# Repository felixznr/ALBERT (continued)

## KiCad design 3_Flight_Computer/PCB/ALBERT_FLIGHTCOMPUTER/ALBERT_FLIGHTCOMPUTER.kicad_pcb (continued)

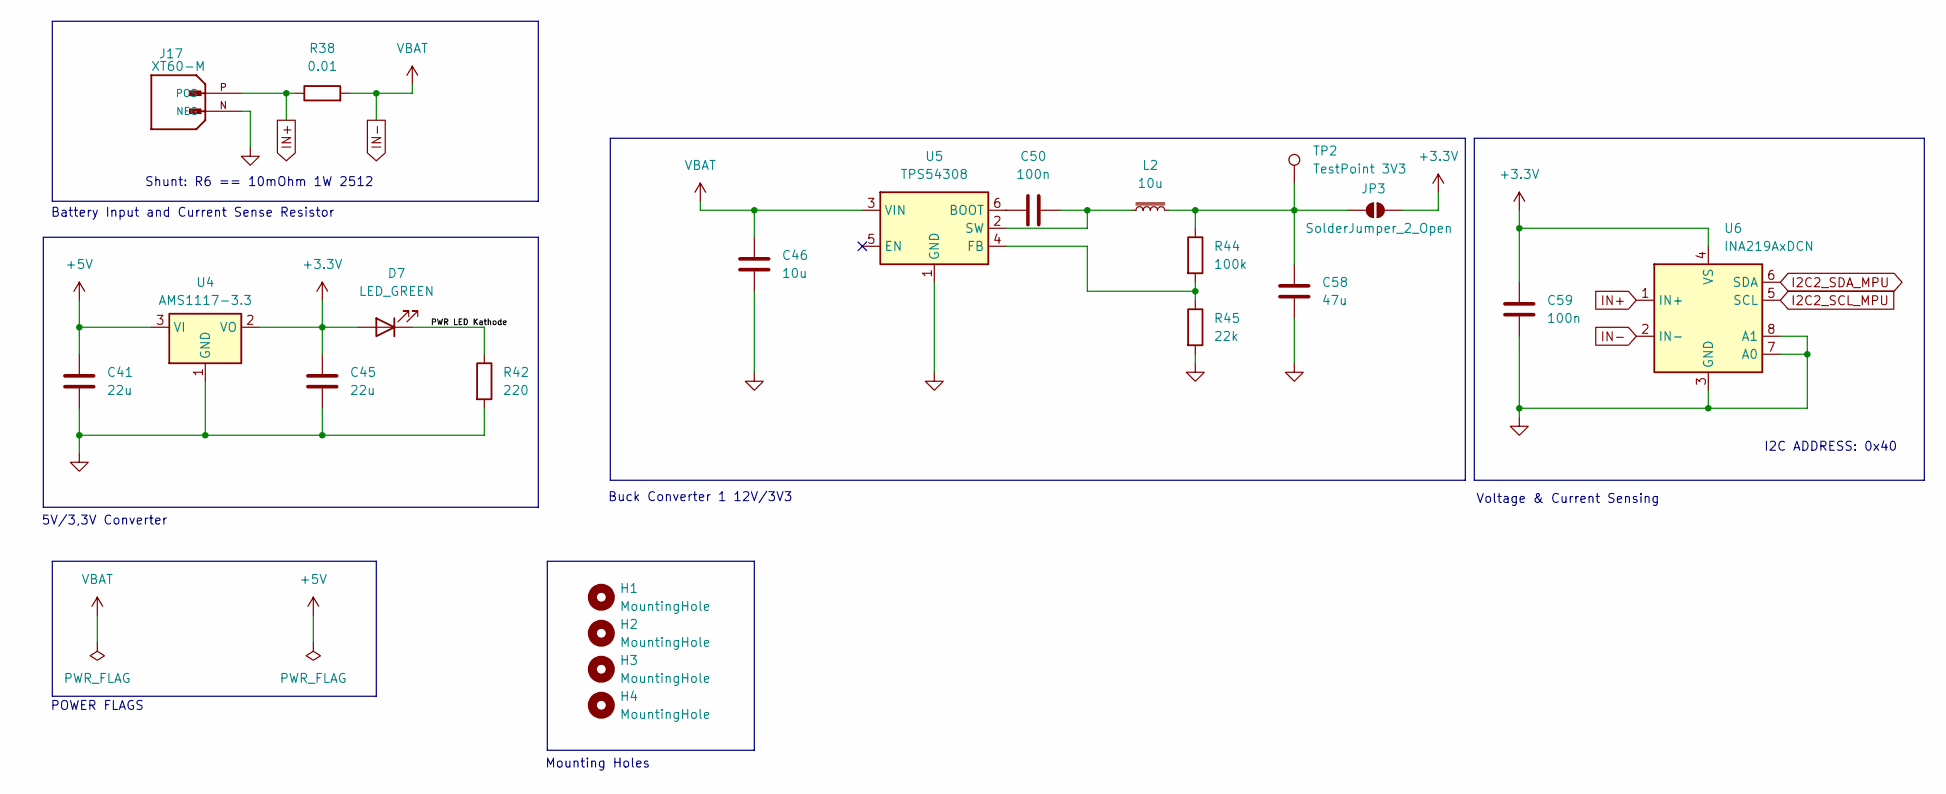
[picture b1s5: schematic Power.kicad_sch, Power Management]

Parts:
C41, C45: 22u; C_0805_2012Metric; LCSC C45783
C46: 10u; CAPC3225X270N; LCSC C380537
C50, C59: 100n; C_0402_1005Metric; LCSC C1525
C58: 47u; CAPC3225X270N; LCSC C77101
D7: LED_GREEN; LED_0603_1608Metric
H1, H2, H3, H4: MountingHole; MountingHole_3.2mm_M3
J17: XT60-M; AMASS_XT60-M; PARTREV V1.2; LCSC C98733
JP3: SolderJumper_2_Open; SolderJumper-2_P1.3mm_Open_RoundedPad1.0x1.5mm
L2: 10u; XAL5050822MEC; LCSC C5309356
R38: 0.01; R_2512_6332Metric; LCSC C316229
R42: 220; R_0402_1005Metric; LCSC C25091
R44: 100k; R_0402_1005Metric; LCSC C25741
R45: 22k; R_0402_1005Metric; LCSC C25768
TP2: TestPoint 3V3; TestPoint_Pad_D2.5mm
U4: AMS1117-3.3; SOT-223-3_TabPin2; LCSC C6186
U5: TPS54308; SOT-23-6; LCSC C168839
U6: INA219AxDCN; SOT-23-8; LCSC C87469

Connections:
+3.3V: C45.1, C59.1, D7.2 (A), JP3.2 (B), U4.2 (VO), U6.4 (VS); also elsewhere on the board
+5V: C41.1, U4.3 (VI); also elsewhere on the board
/Power Management/PWR LED Kathode: D7.1 (K), R42.1
GND: C41.2, C45.2, C46.2, C58.2, C59.2, J17.N (NEG), R42.2, R45.2, U4.1 (GND), U5.1 (GND), U6.3 (GND), U6.7 (A0), U6.8 (A1); also elsewhere on the board
I2C2_SCL_MPU: U6.5 (SCL); also elsewhere on the board
I2C2_SDA_MPU: U6.6 (SDA); also elsewhere on the board
IN+: J17.P (POS), R38.1, U6.1 (IN+)
IN-: C46.1, R38.2, U5.3 (VIN), U6.2 (IN-); also elsewhere on the board
unnamed: C58.1, JP3.1 (A), L2.2, R44.1, TP2.1
unnamed: C50.1, U5.6 (BOOT)
unnamed: R44.2, R45.1, U5.4 (FB)
unnamed: C50.2, L2.1, U5.2 (SW)

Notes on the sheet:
Mounting Holes
POWER FLAGS
5V/3,3V Converter
Battery Input and Current Sense Resistor
Buck Converter 1 12V/3V3
I2C ADDRESS: 0x40
Voltage & Current Sensing
Shunt: R6 == 10mOhm 1W 2512

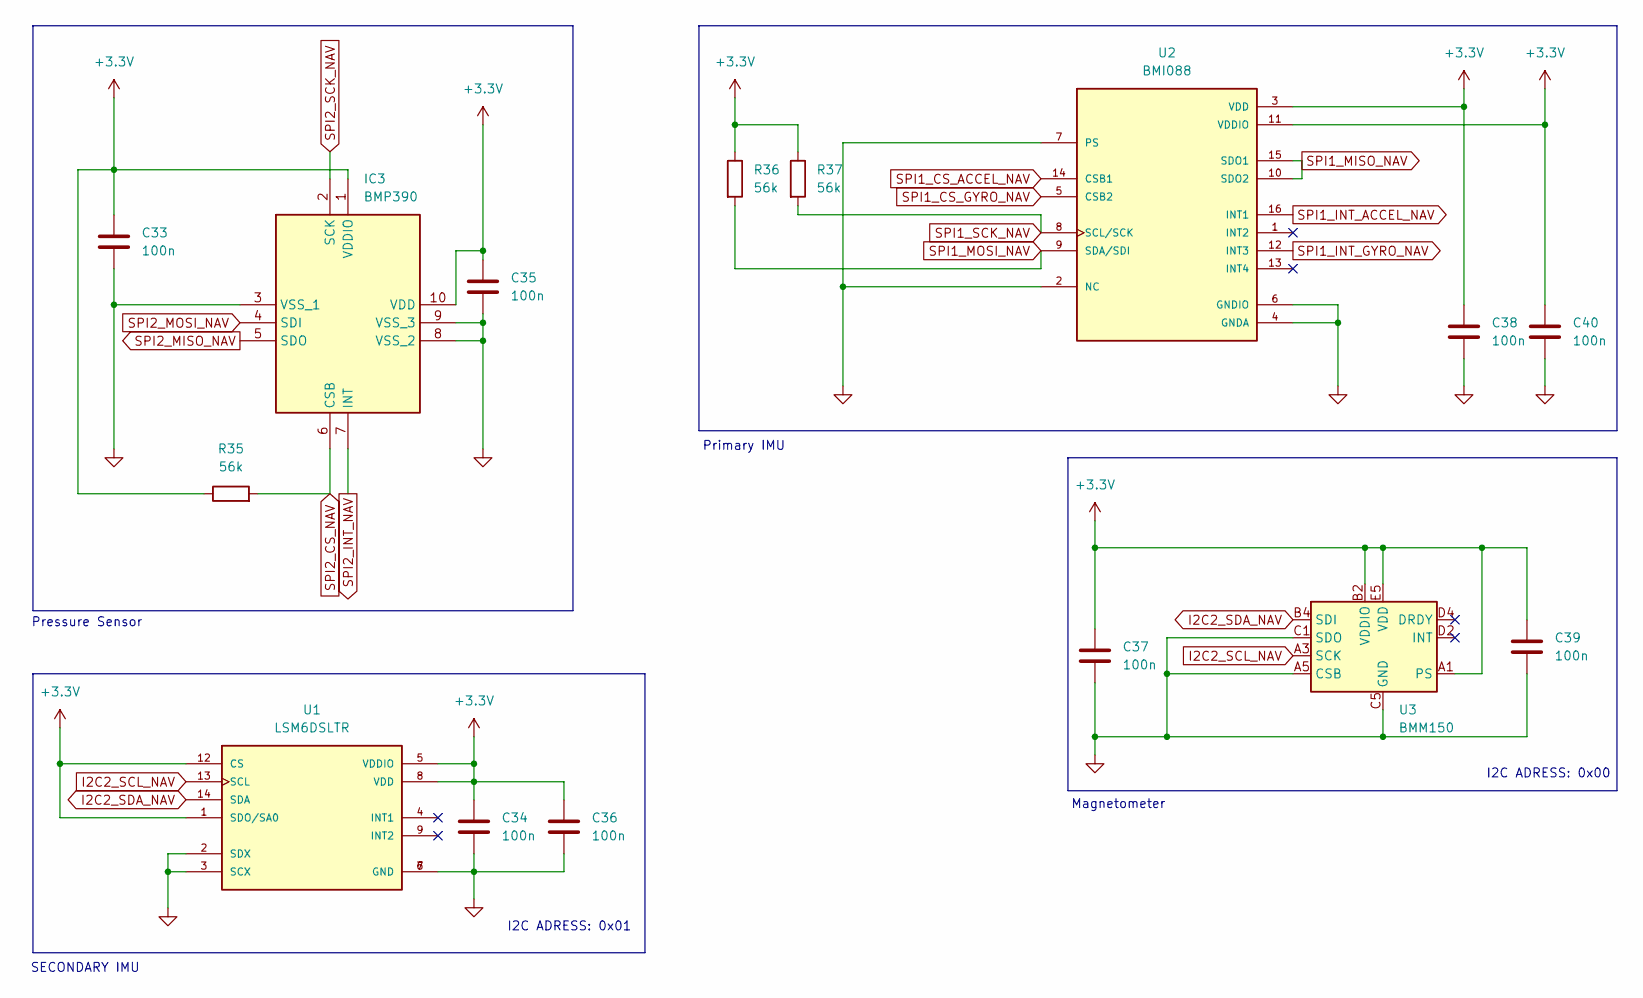
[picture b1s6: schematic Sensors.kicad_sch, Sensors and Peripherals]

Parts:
C33, C34, C35, C36, C37, C38, C39, C40: 100n; C_0402_1005Metric; LCSC C1525
IC3: BMP390; Mouser Part Number 262-BMP390
R35, R36, R37: 56k; R_0402_1005Metric; LCSC C25796
U1: LSM6DSLTR; PQFN50P300X250X86-14N; PARTREV 7; LCSC C126672
U2: BMI088; PQFN50P450X300X100-16N; LCSC C194919
U3: BMM150; WLCSP-12_1.56x1.56mm_P0.4mm; LCSC C171681

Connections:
+3.3V: C33.1, C34.1, C35.1, C36.1, C37.1, C38.1, C39.1, C40.1, IC3.1 (VDDIO), IC3.10 (VDD), R35.1, R36.1, R37.1, U1.1 (SDO/SA0), U1.5 (VDDIO), U1.8 (VDD), U1.12 (CS), U2.3 (VDD), U2.11 (VDDIO), U3.A1 (PS), U3.B2 (VDDIO), U3.E5 (VDD); also elsewhere on the board
GND: C33.2, C34.2, C35.2, C36.2, C37.2, C38.2, C39.2, C40.2, IC3.3 (VSS_1), IC3.8 (VSS_2), IC3.9 (VSS_3), U1.2 (SDX), U1.3 (SCX), U1.6 (GND), U1.7 (GND), U2.2 (NC), U2.4 (GNDA), U2.6 (GNDIO), U2.7 (PS), U3.A5 (CSB), U3.C1 (SDO), U3.C5 (GND), U3.E1 (GND), U3.E3 (GND); also elsewhere on the board
I2C2_SCL_NAV: U1.13 (SCL), U3.A3 (SCK); also elsewhere on the board
I2C2_SDA_NAV: U1.14 (SDA), U3.B4 (SDI); also elsewhere on the board
SPI1_CS_ACCEL_NAV: U2.14 (CSB1); also elsewhere on the board
SPI1_CS_GYRO_NAV: U2.5 (CSB2); also elsewhere on the board
SPI1_INT_ACCEL_NAV: U2.16 (INT1); also elsewhere on the board
SPI1_INT_GYRO_NAV: U2.12 (INT3); also elsewhere on the board
SPI1_MISO_NAV: U2.10 (SDO2), U2.15 (SDO1); also elsewhere on the board
SPI1_MOSI_NAV: R36.2, U2.9 (SDA/SDI); also elsewhere on the board
SPI1_SCK_NAV: R37.2, U2.8 (SCL/SCK); also elsewhere on the board
SPI2_CS_NAV: IC3.6 (CSB), R35.2; also elsewhere on the board
SPI2_INT_NAV: IC3.7 (INT); also elsewhere on the board
SPI2_MISO_NAV: IC3.5 (SDO); also elsewhere on the board
SPI2_MOSI_NAV: IC3.4 (SDI); also elsewhere on the board
SPI2_SCK_NAV: IC3.2 (SCK); also elsewhere on the board

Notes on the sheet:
Primary IMU
I2C ADRESS: 0x01
I2C ADRESS: 0x00
Magnetometer
Pressure Sensor
SECONDARY IMU

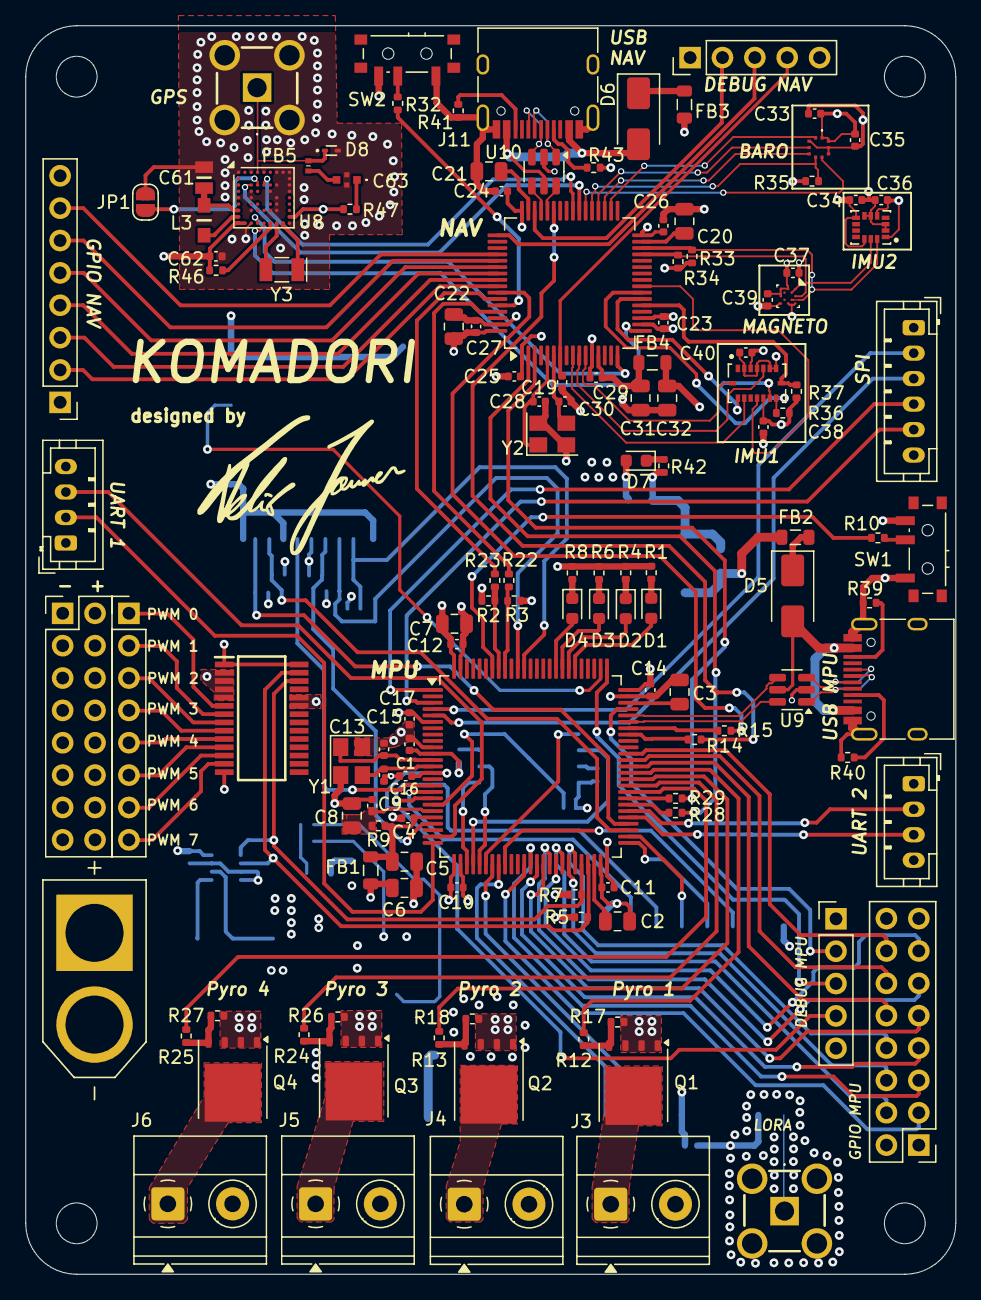
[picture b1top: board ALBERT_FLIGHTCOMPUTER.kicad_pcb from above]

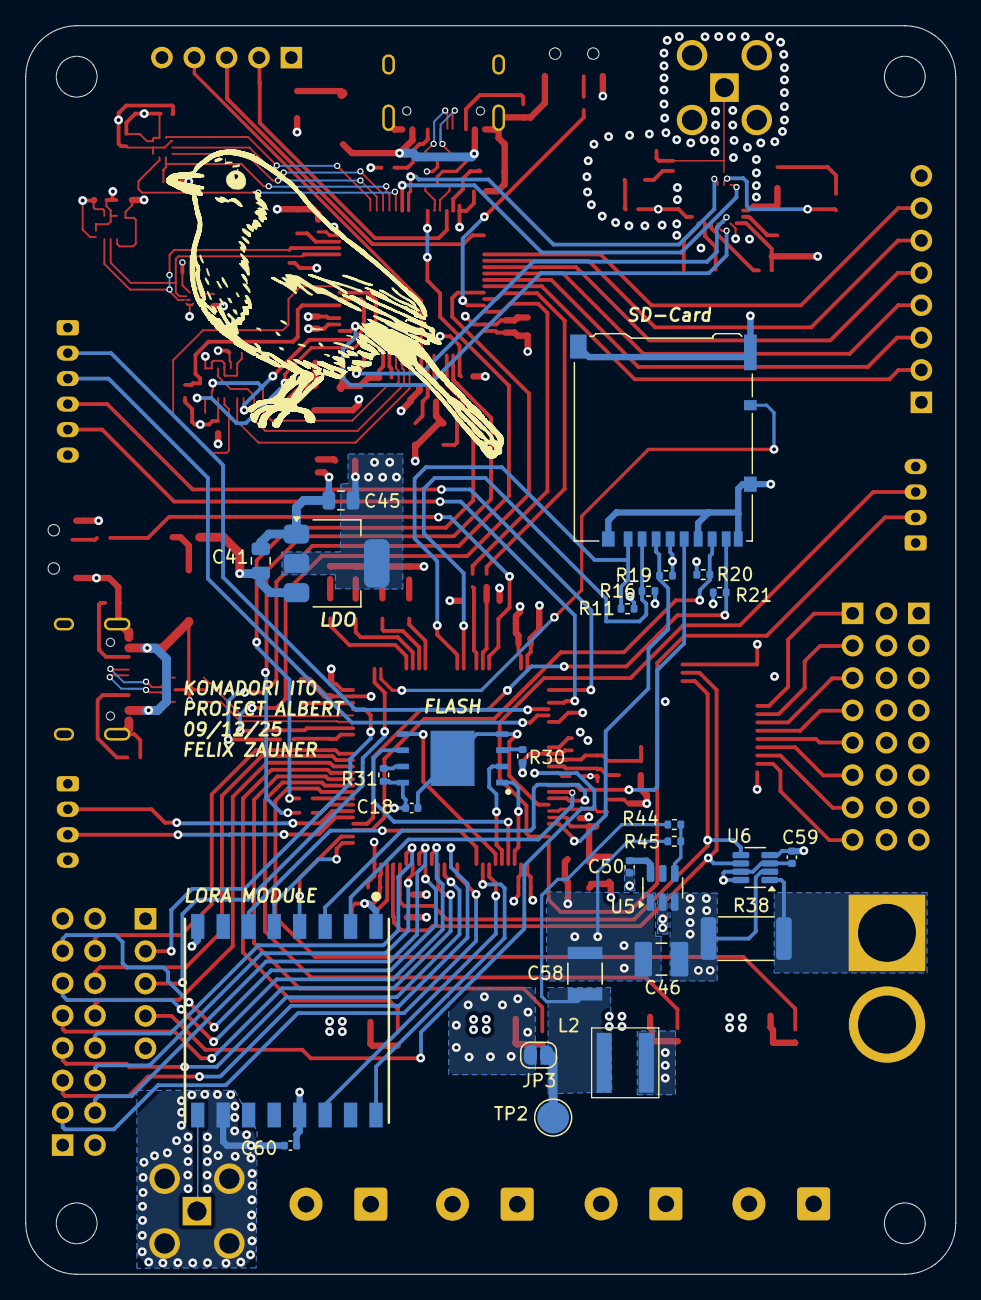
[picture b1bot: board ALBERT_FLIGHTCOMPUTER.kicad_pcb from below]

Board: 4 copper layers, 73.0 x 98.0 mm, 162 parts (27 on the bottom side), 163 nets.

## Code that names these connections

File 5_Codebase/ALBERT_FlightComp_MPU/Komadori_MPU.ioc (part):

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Mcu.Name=STM32H753VITx
Mcu.Package=LQFP100
Mcu.UserName=STM32H753VITx
PA10.GPIOParameters=GPIO_Label
PA10.GPIO_Label=USART1_RX_MPU
PA10.Mode=Asynchronous
PA10.Signal=USART1_RX
PA11.GPIOParameters=GPIO_Label
PA11.GPIO_Label=USB_D-_MPU
PA11.Mode=Device_Only
PA11.Signal=USB_OTG_FS_DM
PA12.GPIOParameters=GPIO_Label
PA12.GPIO_Label=USB_D+_MPU
PA12.Mode=Device_Only
PA12.Signal=USB_OTG_FS_DP
PA13\ (JTMS/SWDIO).GPIOParameters=GPIO_Label
PA13\ (JTMS/SWDIO).GPIO_Label=SWDIO_MPU
PA13\ (JTMS/SWDIO).Mode=Serial_Wire
PA13\ (JTMS/SWDIO).Signal=DEBUG_JTMS-SWDIO
PA14\ (JTCK/SWCLK).GPIOParameters=GPIO_Label
PA14\ (JTCK/SWCLK).GPIO_Label=SWCLK_MPU
PA14\ (JTCK/SWCLK).Mode=Serial_Wire
PA14\ (JTCK/SWCLK).Signal=DEBUG_JTCK-SWCLK
PA15\ (JTDI).GPIOParameters=GPIO_Label
PA15\ (JTDI).GPIO_Label=SD_DET_MPU
PA15\ (JTDI).Signal=GPIO_Input
PA2.GPIOParameters=GPIO_Label
PA2.GPIO_Label=USART2_TX_MPU
PA2.Mode=Asynchronous
PA2.Signal=USART2_TX
PA3.GPIOParameters=GPIO_Label
PA3.GPIO_Label=USART2_RX_MPU
PA3.Mode=Asynchronous
PA3.Signal=USART2_RX
PA4.GPIOParameters=PinState,GPIO_Label
PA4.GPIO_Label=SPI1_CS_MPU
PA4.PinState=GPIO_PIN_SET
PA4.Signal=GPIO_Output
PA5.GPIOParameters=GPIO_Speed,GPIO_PuPd,GPIO_Mode
PA5.GPIO_Mode=GPIO_MODE_AF_PP
PA5.GPIO_PuPd=GPIO_NOPULL
PA5.GPIO_Speed=GPIO_SPEED_FREQ_LOW
PA5.Mode=Full_Duplex_Master
PA5.Signal=SPI1_SCK
PA6.GPIOParameters=GPIO_Speed,GPIO_PuPd,GPIO_Mode
PA6.GPIO_Mode=GPIO_MODE_AF_PP
PA6.GPIO_PuPd=GPIO_NOPULL
PA6.GPIO_Speed=GPIO_SPEED_FREQ_LOW
PA6.Mode=Full_Duplex_Master
PA6.Signal=SPI1_MISO
PA7.GPIOParameters=GPIO_Speed,GPIO_PuPd,GPIO_Mode
PA7.GPIO_Mode=GPIO_MODE_AF_PP
PA7.GPIO_PuPd=GPIO_NOPULL
PA7.GPIO_Speed=GPIO_SPEED_FREQ_LOW
PA7.Mode=Full_Duplex_Master
PA7.Signal=SPI1_MOSI
PA9.GPIOParameters=GPIO_Label
PA9.GPIO_Label=USART1_TX_MPU
PA9.Mode=Asynchronous
PA9.Signal=USART1_TX
PB0.GPIOParameters=GPIO_Label
PB0.GPIO_Label=LORA_RST_MPU
PB0.Signal=GPIO_Output
PB10.GPIOParameters=GPIO_Label
PB10.GPIO_Label=I2C2_SCL_MPU
PB10.Mode=I2C
PB10.Signal=I2C2_SCL
PB11.GPIOParameters=GPIO_Label
PB11.GPIO_Label=I2C2_SDA_MPU
PB11.Mode=I2C
PB11.Signal=I2C2_SDA
PB12.GPIOParameters=GPIO_Label
PB12.GPIO_Label=SPI2_NSS_MPU
PB12.Mode=NSS_Signal_Hard_Output
PB12.Signal=SPI2_NSS
PB13.GPIOParameters=GPIO_Label
PB13.GPIO_Label=SPI2_SCK_MPU
PB13.Mode=Full_Duplex_Master
PB13.Signal=SPI2_SCK
PB6.GPIOParameters=GPIO_Label
PB6.GPIO_Label=I2C1_SCL_MPU
PB6.Mode=I2C
PB6.Signal=I2C1_SCL
PB7.GPIOParameters=GPIO_Label
PB7.GPIO_Label=I2C1_SDA_MPU
PB7.Mode=I2C
PB7.Signal=I2C1_SDA
PC2_C.GPIOParameters=GPIO_Label
PC2_C.GPIO_Label=SPI2_MISO_MPU
PC2_C.Mode=Full_Duplex_Master
PC2_C.Signal=SPI2_MISO
PC3_C.GPIOParameters=GPIO_Label
PC3_C.GPIO_Label=SPI2_MOSI_MPU
PC3_C.Mode=Full_Duplex_Master
PC3_C.Signal=SPI2_MOSI
PC4.GPIOParameters=GPIO_Label
PC4.GPIO_Label=SPI2_DIO0_MPU
PC4.Signal=GPIO_Input
PC5.GPIOParameters=GPIO_Label
PC5.GPIO_Label=SPI2_DIO2_MPU
PC5.Signal=GPIO_Input
PC6.GPIOParameters=GPIO_Label
PC6.GPIO_Label=GPIO10_MPU
PC6.Signal=GPIO_Output
PC7.GPIOParameters=GPIO_Label
PC7.GPIO_Label=GPIO11_MPU
PC7.Signal=GPIO_Output
PC8.GPIOParameters=GPIO_Label
PC8.GPIO_Label=GPIO12_MPU
PC8.Signal=GPIO_Output
PD0.GPIOParameters=GPIO_Label
PD0.GPIO_Label=LED1_MPU
PD0.Signal=GPIO_Output
PD1.GPIOParameters=GPIO_Label
PD1.GPIO_Label=LED2_MPU
PD1.Signal=GPIO_Output
PD10.GPIOParameters=GPIO_Label
PD10.GPIO_Label=INT1_MPU
PD10.Signal=GPIO_Output
PD11.GPIOParameters=GPIO_Label
PD11.GPIO_Label=INT2_MPU
PD11.Signal=GPXTI11
PD12.GPIOParameters=GPIO_Label
PD12.GPIO_Label=Pyro_4_MPU
PD12.Signal=GPIO_Output
PD13.GPIOParameters=GPIO_Label
PD13.GPIO_Label=Pyro_3_MPU
PD13.Signal=GPIO_Output
PD14.GPIOParameters=GPIO_Label
PD14.GPIO_Label=Pyro_2_MPU
PD14.Signal=GPIO_Output
PD15.GPIOParameters=GPIO_Label
PD15.GPIO_Label=Pyro_1_MPU
PD15.Signal=GPIO_Output
PD2.GPIOParameters=GPIO_Label
PD2.GPIO_Label=LED3_MPU
PD2.Signal=GPIO_Output
PD3.GPIOParameters=GPIO_Label
PD3.GPIO_Label=LED4_MPU
PD3.Signal=GPIO_Output
PD8.Mode=Asynchronous
PD8.Signal=USART3_TX
PD9.Mode=Asynchronous
PD9.Signal=USART3_RX
PE10.GPIOParameters=GPIO_Label
PE10.GPIO_Label=GPIO4_MPU
PE10.Signal=GPIO_Output
PE11.GPIOParameters=GPIO_Label
PE11.GPIO_Label=GPIO5_MPU
PE11.Signal=GPIO_Output
PE12.GPIOParameters=GPIO_Label
PE12.GPIO_Label=GPIO6_MPU
PE12.Signal=GPIO_Output
PE13.GPIOParameters=GPIO_Label
PE13.GPIO_Label=GPIO7_MPU
PE13.Signal=GPIO_Output
PE14.GPIOParameters=GPIO_Label
PE14.GPIO_Label=GPIO8_MPU
PE14.Signal=GPIO_Output
PE15.GPIOParameters=GPIO_Label
PE15.GPIO_Label=GPIO9_MPU
PE15.Signal=GPIO_Output
PE2.GPIOParameters=GPIO_Label
PE2.GPIO_Label=SPI4_SCK_MPU
PE2.Mode=Full_Duplex_Master
PE2.Signal=SPI4_SCK
PE4.GPIOParameters=GPIO_Label
PE4.GPIO_Label=SPI4_NSS_MPU
PE4.Mode=NSS_Signal_Hard_Output
PE4.Signal=SPI4_NSS
PE5.GPIOParameters=GPIO_Label
PE5.GPIO_Label=SPI4_MISO_MPU
PE5.Mode=Full_Duplex_Master
PE5.Signal=SPI4_MISO
PE6.GPIOParameters=GPIO_Label
PE6.GPIO_Label=SPI4_MOSI_MPU
PE6.Mode=Full_Duplex_Master
PE6.Signal=SPI4_MOSI
PE7.GPIOParameters=GPIO_Label
PE7.GPIO_Label=GPIO1_MPU
PE7.Signal=GPIO_Output
PE8.GPIOParameters=GPIO_Label
PE8.GPIO_Label=GPIO2_MPU
PE8.Signal=GPIO_Output
PE9.GPIOParameters=GPIO_Label
PE9.GPIO_Label=GPIO3_MPU
PE9.Signal=GPIO_Output
PH0-OSC_IN\ (PH0).GPIOParameters=GPIO_Label
PH0-OSC_IN\ (PH0).GPIO_Label=HSE_IN_MPU
PH0-OSC_IN\ (PH0).Mode=HSE-External-Oscillator
PH0-OSC_IN\ (PH0).Signal=RCC_OSC_IN
PH1-OSC_OUT\ (PH1).GPIOParameters=GPIO_Label
PH1-OSC_OUT\ (PH1).GPIO_Label=HSE_OUT_MPU
PH1-OSC_OUT\ (PH1).Mode=HSE-External-Oscillator
PH1-OSC_OUT\ (PH1).Signal=RCC_OSC_OUT
RCC.HSE_VALUE=16000000
RCC.SYSCLKFreq_VALUE=80000000
RCC.SYSCLKSource=RCC_SYSCLKSOURCE_PLLCLK
board=custom

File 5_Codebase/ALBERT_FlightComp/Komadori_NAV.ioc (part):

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Mcu.Name=STM32F405RGTx
Mcu.Package=LQFP64
Mcu.UserName=STM32F405RGTx
PA10.GPIOParameters=GPIO_Label
PA10.GPIO_Label=USART1_RX_NAV
PA10.Mode=Asynchronous
PA10.Signal=USART1_RX
PA11.GPIOParameters=GPIO_Label
PA11.GPIO_Label=USB_D-_NAV
PA11.Mode=Device_Only
PA11.Signal=USB_OTG_FS_DM
PA12.GPIOParameters=GPIO_Label
PA12.GPIO_Label=USB_D+_NAV
PA12.Mode=Device_Only
PA12.Signal=USB_OTG_FS_DP
PA13.GPIOParameters=GPIO_Label
PA13.GPIO_Label=SWDIO_NAV
PA13.Mode=Serial_Wire
PA13.Signal=SYS_JTMS-SWDIO
PA14.GPIOParameters=GPIO_Label
PA14.GPIO_Label=SWCLK_NAV
PA14.Mode=Serial_Wire
PA14.Signal=SYS_JTCK-SWCLK
PA2.GPIOParameters=GPIO_Label
PA2.GPIO_Label=USART2_TX_NAV
PA2.Mode=Asynchronous
PA2.Signal=USART2_TX
PA3.GPIOParameters=GPIO_Label
PA3.GPIO_Label=USART2_RX_NAV
PA3.Mode=Asynchronous
PA3.Signal=USART2_RX
PA5.GPIOParameters=GPIO_Label
PA5.GPIO_Label=SPI1_SCK_NAV
PA5.Mode=Full_Duplex_Master
PA5.Signal=SPI1_SCK
PA6.GPIOParameters=GPIO_Label
PA6.GPIO_Label=SPI1_MISO_NAV
PA6.Mode=Full_Duplex_Master
PA6.Signal=SPI1_MISO
PA7.GPIOParameters=GPIO_Label
PA7.GPIO_Label=SPI1_MOSI_NAV
PA7.Mode=Full_Duplex_Master
PA7.Signal=SPI1_MOSI
PB10.GPIOParameters=GPIO_Label
PB10.GPIO_Label=I2C2_SCL_NAV
PB10.Mode=I2C
PB10.Signal=I2C2_SCL
PB11.GPIOParameters=GPIO_Label
PB11.GPIO_Label=I2C2_SDA_NAV
PB11.Mode=I2C
PB11.Signal=I2C2_SDA
PB13.GPIOParameters=GPIO_Label
PB13.GPIO_Label=SPI2_SCK_NAV
PB13.Mode=Full_Duplex_Master
PB13.Signal=SPI2_SCK
PB14.GPIOParameters=GPIO_Label
PB14.GPIO_Label=SPI2_MISO_NAV
PB14.Mode=Full_Duplex_Master
PB14.Signal=SPI2_MISO
PB15.GPIOParameters=GPIO_Label
PB15.GPIO_Label=SPI2_MOSI_NAV
PB15.Mode=Full_Duplex_Master
PB15.Signal=SPI2_MOSI
PB3.GPIOParameters=GPIO_Label
PB3.GPIO_Label=GPIO3_NAV
PB3.Signal=GPIO_Output
PB4.GPIOParameters=GPIO_Label
PB4.GPIO_Label=GPIO2_NAV
PB4.Signal=GPIO_Output
PB5.GPIOParameters=GPIO_Label
PB5.GPIO_Label=GPIO1_NAV
PB5.Signal=GPIO_Output
PB6.GPIOParameters=GPIO_Label
PB6.GPIO_Label=USART1_TX_NAV
PB6.Mode=Asynchronous
PB6.Signal=USART1_TX
PB7.GPIOParameters=GPIO_Label
PB7.GPIO_Label=I2C1_SDA_NAV
PB7.Mode=I2C
PB7.Signal=I2C1_SDA
PB8.GPIOParameters=GPIO_Label
PB8.GPIO_Label=I2C1_SCL_NAV
PB8.Mode=I2C
PB8.Signal=I2C1_SCL
PC1.GPIOParameters=GPIO_Label
PC1.GPIO_Label=SPI1_CS_ACCEL_NAV
PC1.Signal=GPIO_Output
PC11.GPIOParameters=GPIO_Label
PC11.GPIO_Label=GPIO6_NAV
PC11.Signal=GPIO_Output
PC12.GPIOParameters=GPIO_Label
PC12.GPIO_Label=GPIO5_NAV
PC12.Signal=GPIO_Output
PC13-ANTI_TAMP.GPIOParameters=GPIO_Label
PC13-ANTI_TAMP.GPIO_Label=INT1_NAV
PC13-ANTI_TAMP.Signal=GPXTI13
PC14-OSC32_IN.GPIOParameters=GPIO_Label
PC14-OSC32_IN.GPIO_Label=INT2_NAV
PC14-OSC32_IN.Signal=GPIO_Output
PC2.GPIOParameters=GPIO_Label
PC2.GPIO_Label=SPI1_CS_GYRO_NAV
PC2.Signal=GPIO_Output
PC3.GPIOParameters=GPIO_Label
PC3.GPIO_Label=SPI1_INT_ACCEL_NAV
PC3.Signal=GPXTI3
PC4.GPIOParameters=GPIO_Label
PC4.GPIO_Label=SPI1_INT_GYRO_NAV
PC4.Signal=GPXTI4
PC6.GPIOParameters=PinState,GPIO_PuPd,GPIO_Label
PC6.GPIO_Label=SPI2_CS_NAV
PC6.GPIO_PuPd=GPIO_PULLDOWN
PC6.PinState=GPIO_PIN_RESET
PC6.Signal=GPIO_Output
PC7.GPIOParameters=GPIO_Label
PC7.GPIO_Label=SPI2_INT_NAV
PC7.Signal=GPXTI7
PC8.GPIOParameters=GPIO_Label
PC8.GPIO_Label=GPS_TP_NAV
PC8.Signal=GPIO_Input
PC9.GPIOParameters=GPIO_Label
PC9.GPIO_Label=GPS_LNA_NAV
PC9.Signal=GPIO_Input
PD2.GPIOParameters=GPIO_Label
PD2.GPIO_Label=GPIO4_NAV
PD2.Signal=GPIO_Output
PH0-OSC_IN.Mode=HSE-External-Oscillator
PH0-OSC_IN.Signal=RCC_OSC_IN
PH1-OSC_OUT.Mode=HSE-External-Oscillator
PH1-OSC_OUT.Signal=RCC_OSC_OUT
RCC.HSE_VALUE=16000000
RCC.SYSCLKFreq_VALUE=168000000
RCC.SYSCLKSource=RCC_SYSCLKSOURCE_PLLCLK
board=custom

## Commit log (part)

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2025-08-03 README.md
2025-08-04 Add CLAUDE.md for ALBERT project overview, goals, and technical specifications
2025-08-04 Refine project objectives and team structure in README.md
2025-08-04 Remove duplicate entry for .gitignore
2025-08-04 Add Albert_prototyp1.ork file to OpenRocket directory
2025-08-04 Add new text files for flight computer, simulation, and codebase
2025-09-29 Add initial files for flight computer and dashboard setup
2025-09-30 Refactor code structure for improved readability and maintainability
2025-11-25 Fix grammar and clarity in Albert I description
    Corrected grammatical errors and improved clarity in the description of Albert I.
2025-11-27 Add lock file for ALBERT_FLIGHTCOMPUTER PCB design
2025-12-01 update pcb
2025-12-02 Add test.zip for ALBERT_FLIGHTCOMPUTER production testing
2025-12-09 Add production files and update project lock file
    - Added new production IT1 zip file for ALBERT_FLIGHTCOMPUTER.
    - Removed obsolete test zip file from production directory.
    - Created a lock file for the KiCad schematic with user and hostname information.
2025-12-11 hallo der papa is da
2025-12-27 update numbero was weiß ich
2025-12-27 big dick randy
2025-12-29 Schaden vor der Bundesrepublik Deutschland abwenden ALTA
2025-12-29 Alltagsgeschichten Wien Favoriten 7258 schilling.mp4
2025-12-30 The Porsche engineers knew exactly what their objective was, to make the new 911 GT2 RS the most powerful Porsche for the road. Objective achieved. The water-cooled 6cyl bi-turbo boxster engine with 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
2025-12-31 My fellow citizens, at this hour, American and coalition forces are in the early stages of military operations to disarm Iraq, to free its people and to defend the world from grave danger.
    On my orders, coalition forces have begun striking selected targets of military importance to undermine Saddam Hussein's ability to wage war. These are opening stages of what will be a broad and conc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
    To all the men a
2026-01-07 Pregnant Women, DON’T USE TYLENOL UNLESS ABSOLUTELY NECESSARY, DON’T GIVE TYLENOL TO YOUR YOUNG CHILD FOR VIRTUALLY ANY REASON, BREAK UP THE MMR SHOT INTO THREE TOTALLY SEPARATE SHOTS (NOT MIXED!), T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
2026-01-07 Ein kleiner Schritt für einen Menschen, ein riesiger Sprung für die Menschheit.
2026-01-09 Кто труда не боится, того лень сторонится.
2026-01-10 "Just keep swimming." \tilde{Dory}
2026-01-10 „Wenn man keine Ahnung hat, einfach mal die Fresse halten"
2026-01-10 tesat ford focus
2026-01-10 Deepseek hure
2026-01-12 Veni, vidi, vici
2026-01-13 pipiquaqua
2026-01-13 neck hurts
2026-01-13 alekjfbsleiufb
2026-01-13 my asshole is burning!
2026-01-13 businessman rich millionaire glory to the rothschilds and rockefellers!!!!!!!!!!!!!!!!!!!!!!!!!!!!!
2026-01-13 royal business marlboro business I MISS THE OLD KANYE STRAIGHT FROM THE GO KANYE CLOUD UP THE SOUL KANYE SET ON HIS GOALS KANYE EFN > ERN
2026-01-14 Baljeet wird abgeschoben Dr. Doofenshmirtz hat ihn beim Asylamt wegen mangelnder Hygiene gemeldet
2026-01-14 businessplan
2026-01-15 meine hoden haben sich verdreht!!!! 🥚🥚🥚🔁🔁🔁
2026-01-15 haben sich wieder entverdreht jetzt bin ich aber steril
2026-01-16 ich sexualisiere persönlichkeitsstörung nicht weil ich mich darüber lustig mache sondern weil ichs geil finde also wenn du borderline hast und amphetaminsüchtig bist bitte piss mir ins maul
2026-01-16 uint8_t times_to_read = 0;
2026-01-17 ich simuliere meinen orgasmus
2026-01-21 openfoam vergewaltigt mich und ich genieße es
2026-02-16 on sum nonchalant type shii
2026-02-18 In der Einleitung zeichnet der Autor ein mit Vorurteilen behaftetes Bild des Gedankengangs eines Gamers, das impliziert, dass die Welt niemals so schön sein könne wie ihr virtueller Zwilling und die 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
2026-02-18 ich sitze im schlauchboot und hol mir einen runter ich muss mich beeilen das schlauchboot geht unter und sind wir dann unten dann holen wir uns nixen denn das ist viel besser als oben zu wichsen
2026-02-18 eier jucken
2026-02-18 commit aus der s3 richtung freilassing
    ich sitze in s3 richtung freilassing
    ich wichs in die sbahn
    sehr leidenschaftlich
    s3 richtung freilassing
2026-02-19 olay
2026-02-19 ich werde mir morgen den 20.02 während dem mühlbacher Unterricht grausam mein leben nehmen
2026-02-19 Bananenkriege (englisch banana wars) ist die umgangssprachliche Sammelbezeichnung für die von den USA Anfang des 20. Jahrhunderts in Mexiko, Mittel- und Südamerika durchgeführten Militäraktionen, die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
2026-02-19 updatos
2026-02-19 was weis ich
2026-02-19 ich pushe die packets versorge die zombies
2026-02-19 penis
2026-02-19 hallo
2026-02-19 https://trace-eu.mediago.io/ju/ic?tn=41b6e88a2b85b0e731ef8e73e5558712&trackingid=de8d407be88eb9c2f1969f38dfe5efe9&acid=749&data=Plv_kTkv9vvgkr5YcuHMCfajtdmbc0RL_XHay3xSVcJWBq83pkMXlWkLWxzG-Y3p8sqpPy6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
2026-02-19 Splish, splash, geh aufs Klo und fick ihn fast Ass fat, waist tiny, only cash Lipgloss, nein, das ist kein Cock-Ring, Bitch Tipptopp, rate mal, was ist das Topping?
2026-02-20 sie sieht aus wie ne türkin bauchnabelpiercing sie hat zwar kleine titten doch ein arsch wie ein pfirsich langes schwarzes haar ihre lippen sind gespritzt wir nehmen sie mit und geben ihr zu dritt
2026-02-21 fett in latex
2026-02-22 https://www.instagram.com/p/DShjznOiK4K/
2026-02-22 5d druck
2026-02-22 das magische einhorn ist es bringt frische haferflocken mit unsichtbaren hühnerfüßen bald ist es soweit!
2026-02-23 ich geh in laden und klau alle hörgeräte
2026-02-24 netherite ingots
2026-02-25 Nordkoreas Machthaber Kim Jong Un ist bei dem alle fünf Jahre stattfindenden Parteitag seiner Arbeiterpartei als Generalsekretär wiedergewählt worden. Die Entscheidung sei am Sonntag "entsprechend de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
2026-02-26 leck eier
2026-02-26 mein gott nochmal
2026-02-26 hingekackt und hingeschissen
2026-02-26 It's freezing and snowing in New York -- we need global warming!
2026-02-26 in meinem garten, in meinem garten blühte blau der rittersporn zwischen dem unkraut in meinem garten im geröll in meinem garten wo die anderen blumen verdorren blumen verdorren
2026-02-26 kein bock auf arbeiten ich bin ein südländer, trick 17 ich mach auf behindert und werd frührentner
2026-02-27 technisches prinzip bei der offenen gasturbine wird umgebungsluft
2026-02-27 aa azzlack original
2026-02-27 wer weiß
2026-02-28 ausdrucken
2026-02-28 so das jz drucken
2026-03-02 „Sternstunden“ der Volks- und Schlagermusik: Das neue DJ ÖTZI Album.2007 kann erst richtig beginnen mit dem neuen DJ ÖTZI Album: Er ist der bekannteste Export aus Österreich und seit Jahren ein Garan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
2026-03-02 Dale a tu cuerpo alegría, Macarena Que tu cuerpo es pa' darle alegría y cosa buena Dale a tu cuerpo alegría, Macarena Hey Macarena, ay! Dale a tu cuerpo alegría, Macarena Que tu cuerpo es pa' darle a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
2026-03-02 #🇯🇵japan is turning footsteps into electricity!
    Using piezoelectric tiles, every step you take generates a small amount of energy. Millions of steps together can power LED lights and displays in busy places like Shibuya Station. A brilliant way to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
2026-03-02 sefsef
2026-03-03 8 hours later, we fired 47 cruise missiles on the iraqi intelligence center. this was at night and we killed the janitor
2026-03-03 John Kiriakou (* 9. August 1964 in Sharon (Pennsylvania)) ist ein ehemaliger US-amerikanischer Geheimdienstler. Er war als Mitarbeiter der Central Intelligence Agency 2002 an der Ergreifung von Abu S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
2026-03-03 pipi und kaka im pipikakaland
2026-03-03 sas soll sas
2026-03-05 na aber hallo
2026-03-07 Quid pro quo; bitch ich kriege einen ständer; bald steht der benz da; sunshine sunshine reggae; bakerman bada bada bada dada is baking bread; subaweya alaboya combagaweja
2026-03-07 ohhhhh
2026-03-11 Masters of the Universe Stamps Orko Moc Blister klar keine cracks Von 1985 sehr selten
2026-03-13 john get the hummus
2026-03-14 DAS IST DER BEWEIS DAS REDO HETERO IST #HETEROMAXXING https://www.instagram.com/reel/DVhIWCiCGmJ/
2026-03-14 ICH MAXXE
2026-03-14 Nackte Hintern, Blowjobs und jede Menge Sex
    Wie dreht man Sexszenen und wer entscheidet, wie viel nackte Haut zu sehen ist?
    Wir haben die Intimitätskoordinatorin der Serie "Heated Rivalry" gefragt.
2026-03-15 ich konfiguriere känguruärsche in meinem innenraumkonfigurator
2026-03-16 git goon --force
2026-03-16 where is my chipotle tiken masala
2026-03-16 freitagsgebet erste reihe mashallah doch ein paar stunden später siehst du wie er hasch ballert
2026-03-17 charlie charlie kirky i just popped a perky
2026-03-17 my crew is big and it keeps getting bigger thats cuz jesus christ is my nigga
2026-03-19 Handgemachte Salzburger Hirschledertracht von Top Qualität sucht einen neuen Träger!
    Zum Verkauf steht die in den Bildern gezeigte Hose.
    Diese wurde von der Trachtenschneiderei Karner in Salzburg mit folgenden Maßen handgefertigt:
    -Bauchumfang 130cm (kann mittels Zwickel noch angepasst werden)
    -Hosenlänge 123cm
    -Schrittlänge 83cm
    Aufgrund dessen, das die Lederhose keine zehnmal getragen wurde, ist diese als neuwertig
2026-03-19 why was 6 afraid of 7 because 7 8 9
2026-03-19 manuel geekhart
2026-03-19 Folgendes Problem ist Matrix gleich Matrix oder Pizza mal Teflon gleich Scorpion Scorpion dreimal Skorpion ja kennst du Unterschied zwischen Scorpion auf Englisch und Scorpion auf Deutsch
2026-03-20 bitte was
2026-03-20 ach scheiß mich an
2026-03-20 big yahu/big stein
2026-03-21 The Big Yahu is a nickname for Israeli Prime Minister Benjamin Netanyahu, most commonly used in memes on TikTok and Instagram Reels. The nickname was popularized in mid-January 2026 by TikToker @gass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
2026-03-23 neurolöwe, ultraneues deutsches surfen, goontrance, deutscher Sprechgesang, tanz-bumm-bumm, meddel leude, englisches reingeträllere, bir, braunes mit braunen blättern, säure-man, vertretbar, fröhlich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
2026-03-23 big yahu x big stein yaoi hentai porn
2026-03-23 TIMMÄÄÄÄÄHHH
2026-03-23 doing it all night all summer gonna spend it like no other
2026-03-23 alcohol, cigarettes and dry humping
2026-03-23 Die EU ruft die Renaissance der Atomkraft aus – und Österreich schreit: "Schleich di!"
2026-03-23 im over here stroking my dick i got lotion on my dick and im over here stroking my shiiiiit man im horny as fuck im a freak
2026-03-23 "Going to Africa. Hope I don't get AIDS. Just kidding. I'm white! " Justine Sacco
2026-03-24 Teststoff für Test am 08.04.2026 Unternehmensgründung Seite 249-255, Seite 261-283 Finanzierung Seite 286-325
    Ach! und Weh!,
    Mord! Zetter! Jammer / Angst / Kreuz! Marter! Würme! Plagen.
    Pech! Folter! Hencker! Flamm! Stank! Geister! Kälte! Zagen!
    Ach vergeh!
    Tiff’ und Höh’!
    Meer! Hügel! Berge! Fels wer kann die Pein ertragen?
2026-03-24 oida
2026-03-25 Der Papa ist King, doch das heißt nicht, dass du ein Prinz bist Deine Mom ist meine Schwester, richtig, das ist Inzest Ich schüttel' meinen Sohnemann, Kurzer, mach die Augen auf Ich kann dich nicht z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
2026-03-25 ai slop
2026-03-25 cunt ass
2026-03-25 govno
2026-03-25 hallihallo
2026-03-25 ich schneide matlab die kehle durch
2026-03-25 i wanna kms
2026-03-25 ach ich hasse mein leben und hab kein bock mehr
2026-03-25 ich bin ready für die hölle
2026-03-25 ach leck meine eier alles umsonst
2026-03-25 ich steck meinen kopf in den sand wie ein strauß seine hoden
2026-03-25 kopfschuss v2
2026-03-26 ich shamponier wahnsinnig gerne schimpansenarschlöcher ein
2026-03-26 lassy
2026-03-26 ich spüre die freiheit
2026-03-26 sie ist nicht mehr weit weg
2026-03-26 ach ich lieeebe das leeeeeben
2026-03-26 entweder ich hänge mich auf oder ich hänge mich auf
2026-03-27 pre munich turbulenzen
2026-03-27 die zeit ist gekommen meine eier über meine ganze tastatur zu entleeren
2026-04-18 https://www.youtube.com/watch?v=VECKfiO5XPo
2026-04-18 pete am tweaken
2026-04-20 aint that a bitchhhhhhhhhHhhh
2026-04-20 https://www.instagram.com/reel/CjASpZbIfl9/?hl=de
2026-04-20 bello el imposible
2026-04-27 maney
2026-04-28 god forbid a man who doesn't know a resolver sin / cos be a bitch
2026-04-29 There goes my hero
